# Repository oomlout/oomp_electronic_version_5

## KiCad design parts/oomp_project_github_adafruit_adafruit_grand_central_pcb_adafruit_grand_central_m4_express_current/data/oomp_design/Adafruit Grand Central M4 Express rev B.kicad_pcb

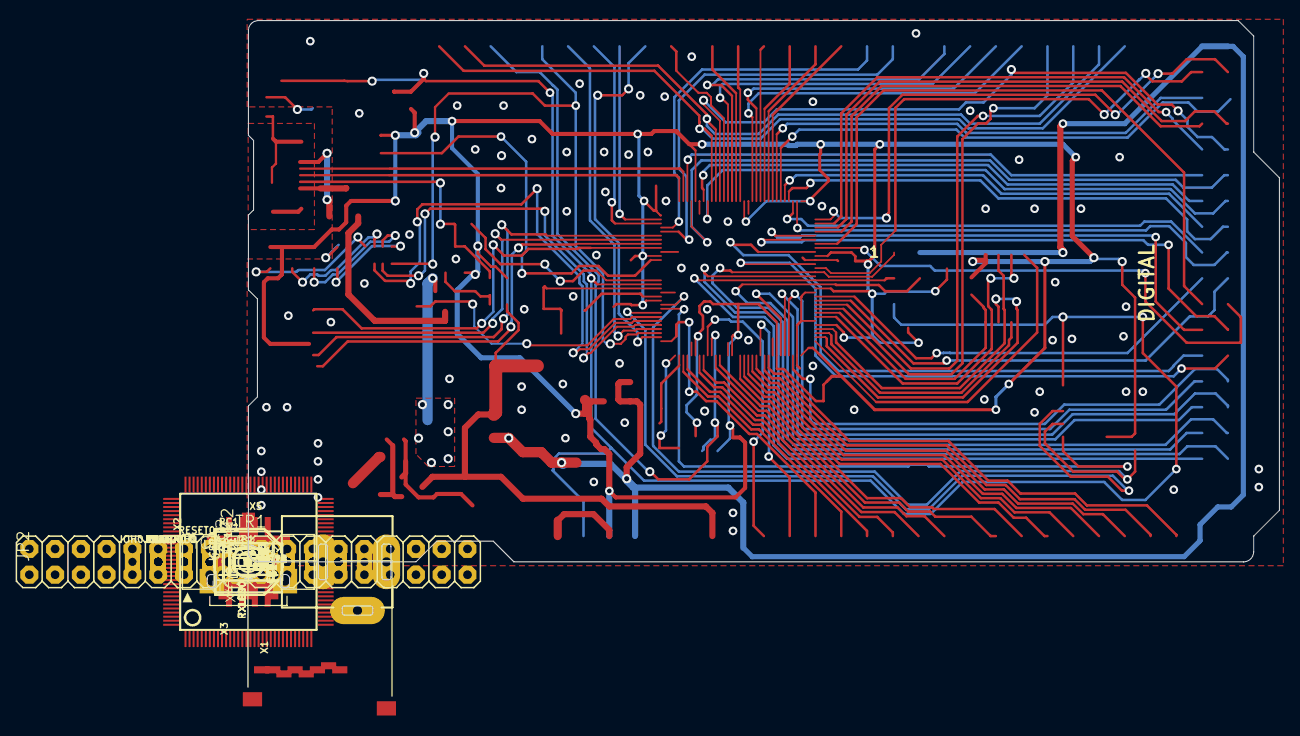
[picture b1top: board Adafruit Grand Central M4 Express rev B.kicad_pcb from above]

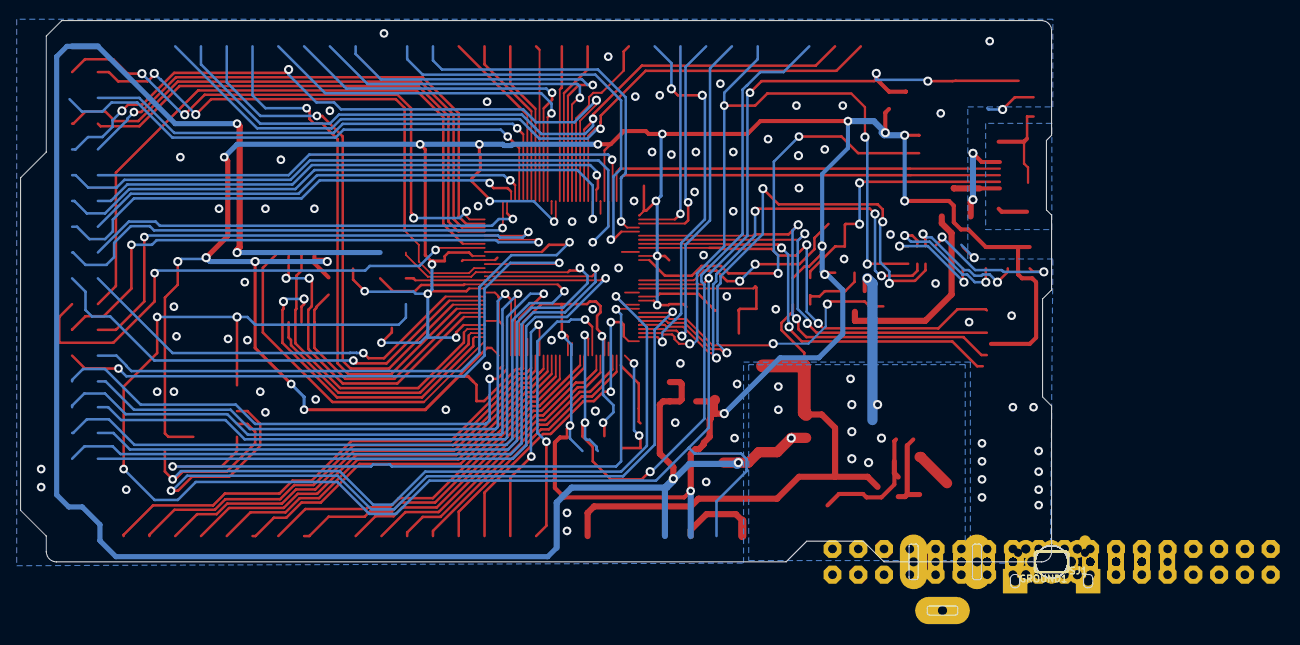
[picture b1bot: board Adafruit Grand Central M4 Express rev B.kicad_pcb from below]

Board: 2 copper layers, 105.7 x 58.6 mm, 81 parts (3 on the bottom side), 113 nets.

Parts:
ANALOGH0: 20610; 1X08_OVALWAVE
ANALOGL0: 20610; 1X08_OVALWAVE
C1, C2, C3: 10uF; 0805-NO
C4, C6, C8, C10, C11, C14, C15, C16, C18, C19, C20, C21, C22, C23, C24, C25: .1u; 0603-NO
C5, C7: 22pF; 0603-NO
C9: 1uF; 0603-NO
C12, C13, C17: 0.1uF; 0603-NO
D1: MBR120; SOD-123
F2: 500mA; R1206
FB2: FERRITE; 0805-NO
FD1, FD2, FD3, FD4, FD5: FIDUCIAL_1MM
GROUND1: SOLDERJUMPER_CLOSEDWIRE
IC3: 74LVC1G125D; SOT23-5
ICSP0: 3x2 M; 2X03_ROUND_70MIL
IOH0: 20611; 1X10_OVALWAVE
IOL0: 20610; 1X08_OVALWAVE
JP1: 1X01_ROUND
JP2: 2X18_THICKWAVE
L0: RED; CHIPLED_0805_NOOUTLINE
L1: 10uH; INDUCTOR_1007
LED1: WS2812B3535; LED3535
ON0: GREEN; CHIPLED_0805_NOOUTLINE
PC1: 47uF/25V; PANASONIC_D
PC2: 47uF+/6.3V+; PANASONIC_D
POWER0: 20610; 1X08_OVALWAVE
R1: 100K; RESPACK_4X0603
R2: 1K; RESPACK_4X0603
R3, R5, R7: 10K; 0603-NO
R4: 1K; 0603-NO
R11: 330R; 0603-NO
RESET0: EVQQ 6mm; EVQ-Q2_SMALLER
RXLED0: YELLOW; CHIPLED_0805_NOOUTLINE
SJ1: AREF_3V; SOLDERJUMPER_CLOSEDWIRE
SW1: SPDT_SMT_SSSS811101
T2: DMP3098L-7; SOT-23
TR1: DMP3098L-7; SOT-23
TXLED0: YELLOW; CHIPLED_0805_NOOUTLINE
U1: NCP1117ST50T3G; SOT223-R
U2: AP2112K-3.3; SOT23-DBV
U3: GD25Q64; SOIC8_208MIL
U$1: SAMD51PXXA; SQFP-S-14X14-128
U$23: GRANDCENTRAL_REVB-BOT
U$30: GRANDCENTRAL_REVB_TOP
UART0: 20610; 1X08_OVALWAVE
UNK_HOLE_0: dummyfp0
UNK_HOLE_1: dummyfp1
UNK_HOLE_2: dummyfp2
UNK_HOLE_3: dummyfp3
UNK_HOLE_4: dummyfp4
UNK_HOLE_5: dummyfp5
X1: microsd; MICROSD
X2: 2x5 0.05" SWD; 2X05_1.27MM_BOX_POSTS
X3: 20329; 4UCONN_20329_V2
X4: 32.768; XTAL3215
X5: 2.1mm; DCJACK_2MM_PTH

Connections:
3.3V: C3.2, C6.2, C10.2, C11.2, C13.1, C14.2, C15.2, C16.2, C18.2, C19.2, C20.2, C21.2, C22.2, C23.2, C24.2, C25.2, IC3.5, LED1.2, ON0.A, POWER0.2, POWER0.4, R1.4, R3.1, R4.2, R5.2, RXLED0.A, SJ1.1, TXLED0.A, U2.5, U3.8, U$1.6, U$1.15, U$1.26, U$1.32, U$1.37, U$1.46, U$1.54, U$1.65, U$1.79, U$1.91, U$1.97, U$1.107, U$1.118, X1.4, X2.1
+5V: C2.2, ICSP0.2, JP2.1, JP2.2, PC2.+, POWER0.5, TR1.2, U1.2, U1.4, U2.1, U2.3
A0: ANALOGL0.1, U$1.9
A1: ANALOGL0.2, U$1.22
A2: ANALOGL0.3, U$1.128
A3: ANALOGL0.4, U$1.3
A4: ANALOGL0.5, U$1.4
A5: ANALOGL0.6, U$1.7
A6: ANALOGL0.7, U$1.8
A7: ANALOGL0.8, U$1.11
A8: ANALOGH0.1, U$1.12
A9: ANALOGH0.2, U$1.17
A10: ANALOGH0.3, U$1.18
A11: ANALOGH0.4, U$1.19
A12: ANALOGH0.5, U$1.20
A13: ANALOGH0.6, U$1.21
A14: ANALOGH0.7, U$1.23
A15: ANALOGH0.8, U$1.24
AREF: C4.1, IOH0.3, SJ1.2, U$1.10
D0: IOL0.8, U$1.101
D1: IOL0.7, U$1.100
D2: IOL0.6, U$1.72
D3: IOL0.5, U$1.73
D4: IOL0.4, U$1.74
D5: IOL0.3, U$1.75
D6: IOL0.2, U$1.80
D7: IOL0.1, U$1.81
D8: IOH0.10, U$1.84
D9: IOH0.9, U$1.127
D10: IOH0.8, U$1.98
D11: IOH0.7, U$1.99
D12: IOH0.6, U$1.125
D13: IOH0.5, R2.8, U$1.126
D22: JP2.3, U$1.51
D23: JP2.4, U$1.63
D44: JP2.25, U$1.55
D45: JP2.26, U$1.52
D46: JP2.27, U$1.29
D47: JP2.28, U$1.30
D48: JP2.29, U$1.27
D49: JP2.30, U$1.28
D+: U$1.95, X3.D+
D-: U$1.94, X3.D-
FLASH_CS: R5.1, U3.1, U$1.40
FLASH_IO0: U3.5, U$1.33
FLASH_IO1: U3.2, U$1.34
FLASH_IO2: U3.3, U$1.35
FLASH_IO3: U3.7, U$1.36
FLASH_SCK: U3.6, U$1.39
GND: C1.2, C2.1, C3.1, C4.2, C5.2, C6.1, C7.2, C8.1, C9.2, C10.1, C11.1, C12.2, C13.2, C14.1, C15.1, C16.1, C17.1, C18.1, C19.1, C20.1, C21.1, C22.1, C23.1, C24.1, C25.1, GROUND1.2, IC3.3, ICSP0.6, IOH0.4, JP2.35, JP2.36, L0.C, LED1.4, PC1.-, PC2.-, POWER0.6, POWER0.7, R1.2, R2.5, RESET0.A, RESET0.A', SW1.A, U1.1, U2.2, U3.4, U$1.5, U$1.14, U$1.25, U$1.31, U$1.38, U$1.45, U$1.53, U$1.64, U$1.78, U$1.90, U$1.96, U$1.106, U$1.116, X1.6, X1.MT1, X1.MT2, X2.3, X2.5, X3.GND, X5.GND, X5.GNDBREAK
MISO: ICSP0.1, JP2.31, U$1.50
MOSI: ICSP0.4, JP2.32, U$1.47
unnamed: L0.A, R2.1
unnamed: FB2.1, GROUND1.1
unnamed: ON0.C, R2.4
unnamed: L1.P$2, U$1.117
unnamed: R2.2, RXLED0.C
unnamed: R2.3, TXLED0.C
unnamed: C5.1, U$1.1, X4.P$1
unnamed: IC3.1, IC3.2, R1.5, R11.1, X3.ID
unnamed: IC3.4, R1.7, R1.8, TR1.3
unnamed: C7.1, U$1.2, X4.P$2
unnamed: D1.C, R7.2, T2.2
NEOPIX: LED1.1, U$1.108
PCC_CLK: JP2.9, U$1.62
PCC_D0: JP2.18, U$1.66
PCC_D1: JP2.17, U$1.67
PCC_D2: JP2.16, U$1.68
PCC_D3: JP2.15, U$1.69
PCC_D4: JP2.14, U$1.88
PCC_D5: JP2.13, U$1.89
PCC_D6: JP2.12, U$1.92
PCC_D7: JP2.11, U$1.93
PCC_D8: JP2.20, U$1.43
PCC_D9: JP2.19, U$1.44
PCC_D10: JP2.22, U$1.56
PCC_D11: JP2.21, U$1.57
PCC_D12: JP2.24, U$1.58
PCC_D13: JP2.23, U$1.59
PCC_DEN1: JP2.7, U$1.60
PCC_DEN2: JP2.8, U$1.61
PCC_XCLK: JP2.10, U$1.85
PWRIN: D1.A, X5.PWR
PWR_SWITCH: JP1.1, R7.1, SW1.B, T2.3
RXLED: R2.7, U$1.124
SCK: ICSP0.3, JP2.33, U$1.48
SCL: IOH0.1, U$1.87, UART0.8
SCL_1: JP2.5, U$1.71
SDA: IOH0.2, U$1.86, UART0.7
SDA_1: JP2.6, U$1.70
SD_CD: U$1.122, X1.CD1
SD_CS: U$1.104, X1.2
SD_MISO: U$1.105, X1.7
SD_MOSI: U$1.102, X1.3
SD_SCK: U$1.103, X1.5
SS: JP2.34, U$1.49
SWCLK: R4.1, U$1.119, X2.4
SWDIO: U$1.120, X2.2
SWO: U$1.121, X2.6
TXLED: R2.6, U$1.123
UART1_RX: U$1.42, UART0.6
UART1_TX: U$1.41, UART0.5
UART2_RX: U$1.77, UART0.4
UART2_TX: U$1.76, UART0.3
UART3_RX: U$1.83, UART0.2
UART3_TX: U$1.82, UART0.1
USBVCC: F2.2, TR1.1
USB_HOSTEN: R11.2, U$1.113
USHIELD: FB2.2, X3.BASE@1, X3.BASE@2, X3.SPRT@1, X3.SPRT@2, X3.SPRT@3, X3.SPRT@4
VBUS: F2.1, X3.VBUS
VDDCORE: C1.1, C8.2, C9.1, L1.P$1, U$1.115
VIN: C12.1, PC1.+, POWER0.8, R1.1, T2.1, U1.3
~RESET: C17.2, ICSP0.5, POWER0.3, R3.2, RESET0.B, RESET0.B', U$1.114, X2.10

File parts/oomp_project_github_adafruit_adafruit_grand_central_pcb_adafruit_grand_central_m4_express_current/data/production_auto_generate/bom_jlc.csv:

Comment,Designator,Footprint,LCSC Part #
,JP1,Adafruit Grand Central M4 Express rev B-import-fps:1X01_ROUND,C7501259
,JP2,Adafruit Grand Central M4 Express rev B-import-fps:2X18_THICKWAVE,
,U$23,Adafruit Grand Central M4 Express rev B-import-fps:GRANDCENTRAL_REVB-BOT,
,U$30,Adafruit Grand Central M4 Express rev B-import-fps:GRANDCENTRAL_REVB_TOP,
,GROUND1,Adafruit Grand Central M4 Express rev B-import-fps:SOLDERJUMPER_CLOSEDWIRE,
,SW1,Adafruit Grand Central M4 Express rev B-import-fps:SPDT_SMT_SSSS811101,
.1u,"C4,C6,C8,C10,C11,C14,C15,C16,C18,C19,C20,C21,C22,C23,C24,C25",Adafruit Grand Central M4 Express rev B-import-fps:0603-NO,
0.1uF,"C12,C13,C17",Adafruit Grand Central M4 Express rev B-import-fps:0603-NO,C14663
100K,R1,Adafruit Grand Central M4 Express rev B-import-fps:RESPACK_4X0603,C25803
10K,"R3,R5,R7",Adafruit Grand Central M4 Express rev B-import-fps:0603-NO,C98220
10uF,"C1,C2,C3",Adafruit Grand Central M4 Express rev B-import-fps:0805-NO,
10uH,L1,Adafruit Grand Central M4 Express rev B-import-fps:INDUCTOR_1007,
1K,R4,Adafruit Grand Central M4 Express rev B-import-fps:0603-NO,C2907002
1K,R2,Adafruit Grand Central M4 Express rev B-import-fps:RESPACK_4X0603,C2907002
1uF,C9,Adafruit Grand Central M4 Express rev B-import-fps:0603-NO,C5673
2.1mm,X5,Adafruit Grand Central M4 Express rev B-import-fps:DCJACK_2MM_PTH,
20329,X3,Adafruit Grand Central M4 Express rev B-import-fps:4UCONN_20329_V2,
20610,"ANALOGH0,ANALOGL0,IOL0,POWER0,UART0",Adafruit Grand Central M4 Express rev B-import-fps:1X08_OVALWAVE,C492421
20611,IOH0,Adafruit Grand Central M4 Express rev B-import-fps:1X10_OVALWAVE,C57369
22pF,"C5,C7",Adafruit Grand Central M4 Express rev B-import-fps:0603-NO,C105620
"2x5 0.05"" SWD",X2,Adafruit Grand Central M4 Express rev B-import-fps:2X05_1.27MM_BOX_POSTS,
32.768,X4,Adafruit Grand Central M4 Express rev B-import-fps:XTAL3215,
330R,R11,Adafruit Grand Central M4 Express rev B-import-fps:0603-NO,C2933198
3x2 M,ICSP0,Adafruit Grand Central M4 Express rev B-import-fps:2X03_ROUND_70MIL,
47uF+/6.3V+,PC2,Adafruit Grand Central M4 Express rev B-import-fps:PANASONIC_D,
47uF/25V,PC1,Adafruit Grand Central M4 Express rev B-import-fps:PANASONIC_D,
500mA,F2,Adafruit Grand Central M4 Express rev B-import-fps:R1206,
74LVC1G125D,IC3,Adafruit Grand Central M4 Express rev B-import-fps:SOT23-5,
AP2112K-3.3,U2,Adafruit Grand Central M4 Express rev B-import-fps:SOT23-DBV,
DMP3098L-7,"T2,TR1",Adafruit Grand Central M4 Express rev B-import-fps:SOT-23,
EVQQ 6mm,RESET0,Adafruit Grand Central M4 Express rev B-import-fps:EVQ-Q2_SMALLER,
FERRITE,FB2,Adafruit Grand Central M4 Express rev B-import-fps:0805-NO,
FIDUCIAL_1MM,"FD1,FD2,FD3,FD4,FD5",Adafruit Grand Central M4 Express rev B-import-fps:FIDUCIAL_1MM,
GD25Q64,U3,Adafruit Grand Central M4 Express rev B-import-fps:SOIC8_208MIL,
GREEN,ON0,Adafruit Grand Central M4 Express rev B-import-fps:CHIPLED_0805_NOOUTLINE,
MBR120,D1,Adafruit Grand Central M4 Express rev B-import-fps:SOD-123,
microsd,X1,Adafruit Grand Central M4 Express rev B-import-fps:MICROSD,
NCP1117ST50T3G,U1,Adafruit Grand Central M4 Express rev B-import-fps:SOT223-R,
RED,L0,Adafruit Grand Central M4 Express rev B-import-fps:CHIPLED_0805_NOOUTLINE,
SAMD51PXXA,U$1,Adafruit Grand Central M4 Express rev B-import-fps:SQFP-S-14X14-128,
WS2812B3535,LED1,Adafruit Grand Central M4 Express rev B-import-fps:LED3535,
YELLOW,"RXLED0,TXLED0",Adafruit Grand Central M4 Express rev B-import-fps:CHIPLED_0805_NOOUTLINE,

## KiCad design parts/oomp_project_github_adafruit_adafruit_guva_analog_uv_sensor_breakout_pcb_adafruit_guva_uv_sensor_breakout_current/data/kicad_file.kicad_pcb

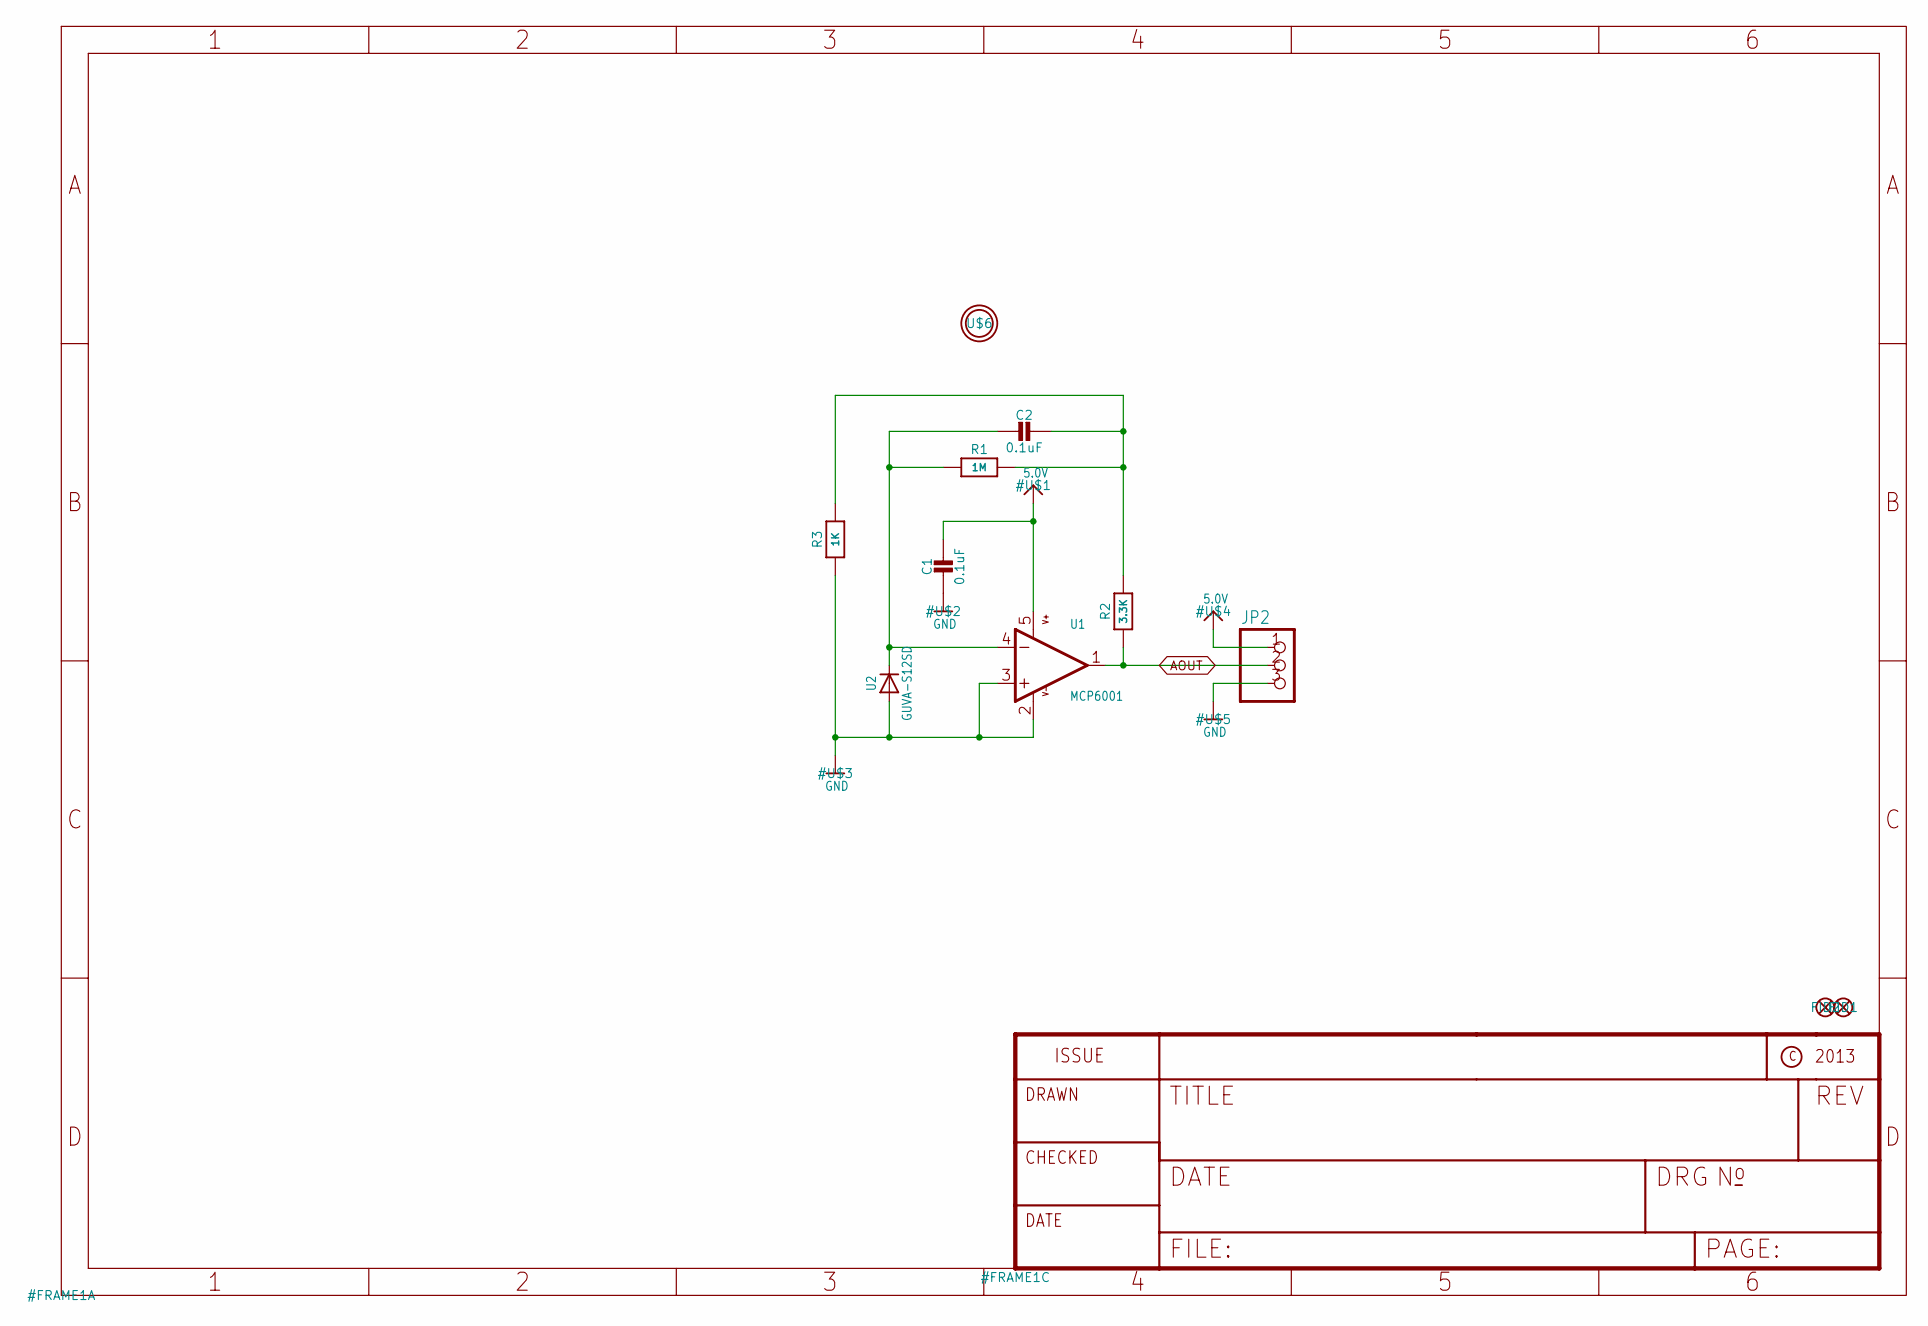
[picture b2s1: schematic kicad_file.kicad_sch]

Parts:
C1, C2: 0.1uF; 0805-NO
FID1, FID2: FIDUCIAL""; FIDUCIAL_1MM
JP2: PINHD-1X3CB; 1X03-CLEANBIG
R1: 1M; 0805-NO
R2: 3.3K; 0805-NO
R3: 1K; 0805-NO
U1: MCP6001; SOT23-5
U2: GUVA-S12SD
U$6: MOUNTINGHOLE2.5; MOUNTINGHOLE_2.5_PLATED

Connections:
5.0V: C1.1, JP2.1, U1.5 (V+)
AOUT: JP2.2, R2.1, U1.1 (OUT)
GND: C1.2, JP2.3, R3.1, U1.2 (V-), U1.3 (+IN), U2.A
unnamed: C2.1, R1.2, R2.2, R3.2
unnamed: C2.2, R1.1, U1.4 (-IN), U2.K (C)

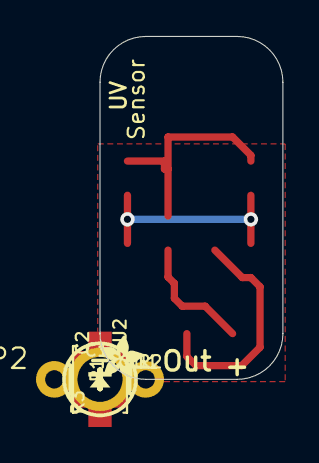
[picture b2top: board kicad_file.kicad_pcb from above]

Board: 2 copper layers, 10.2 x 19.1 mm, 13 parts (1 on the bottom side), 5 nets.

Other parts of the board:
U$7, U$8: ADAFRUIT_2.5MM

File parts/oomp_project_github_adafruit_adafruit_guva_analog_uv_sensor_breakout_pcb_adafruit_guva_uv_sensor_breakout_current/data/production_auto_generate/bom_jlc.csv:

Comment,Designator,Footprint,LCSC Part #
,JP2,Adafruit GUVA UV Sensor Breakout-import-fps:1X03-CLEANBIG,C49257
,"U$7,U$8",Adafruit GUVA UV Sensor Breakout-import-fps:ADAFRUIT_2.5MM,
0.1uF,"C1,C2",Adafruit GUVA UV Sensor Breakout-import-fps:0805-NO,
1K,R3,Adafruit GUVA UV Sensor Breakout-import-fps:0805-NO,C17513
1M,R1,Adafruit GUVA UV Sensor Breakout-import-fps:0805-NO,C2933280
3.3K,R2,Adafruit GUVA UV Sensor Breakout-import-fps:0805-NO,C2907249
GUVA-S12SD,U2,Adafruit GUVA UV Sensor Breakout-import-fps:GUVA-S12SD,
MCP6001,U1,Adafruit GUVA UV Sensor Breakout-import-fps:SOT23-5,

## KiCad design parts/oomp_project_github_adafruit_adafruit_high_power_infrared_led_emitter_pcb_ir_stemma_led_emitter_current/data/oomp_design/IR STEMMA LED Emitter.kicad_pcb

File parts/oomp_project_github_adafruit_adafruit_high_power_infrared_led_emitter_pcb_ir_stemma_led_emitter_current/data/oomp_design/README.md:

# OOMP KiCad design copy

Open `IR STEMMA LED Emitter.kicad_pro` (or the `.kicad_pcb` / `.kicad_sch`) in KiCad. Local OOMP libraries are under `libraries/`. Original inputs are preserved in [../original/](../original/).

Only verified unchanged installed KiCad defaults were renamed. Modified, custom, unmatched and unavailable items remain unchanged. Soldering variants are never swapped during conversion. Existing pad coordinates, nets and UUIDs are preserved.

See [conversion_report.yaml](conversion_report.yaml) for every conversion and skip. Copy this directory before editing; regeneration refuses to overwrite edited design files.

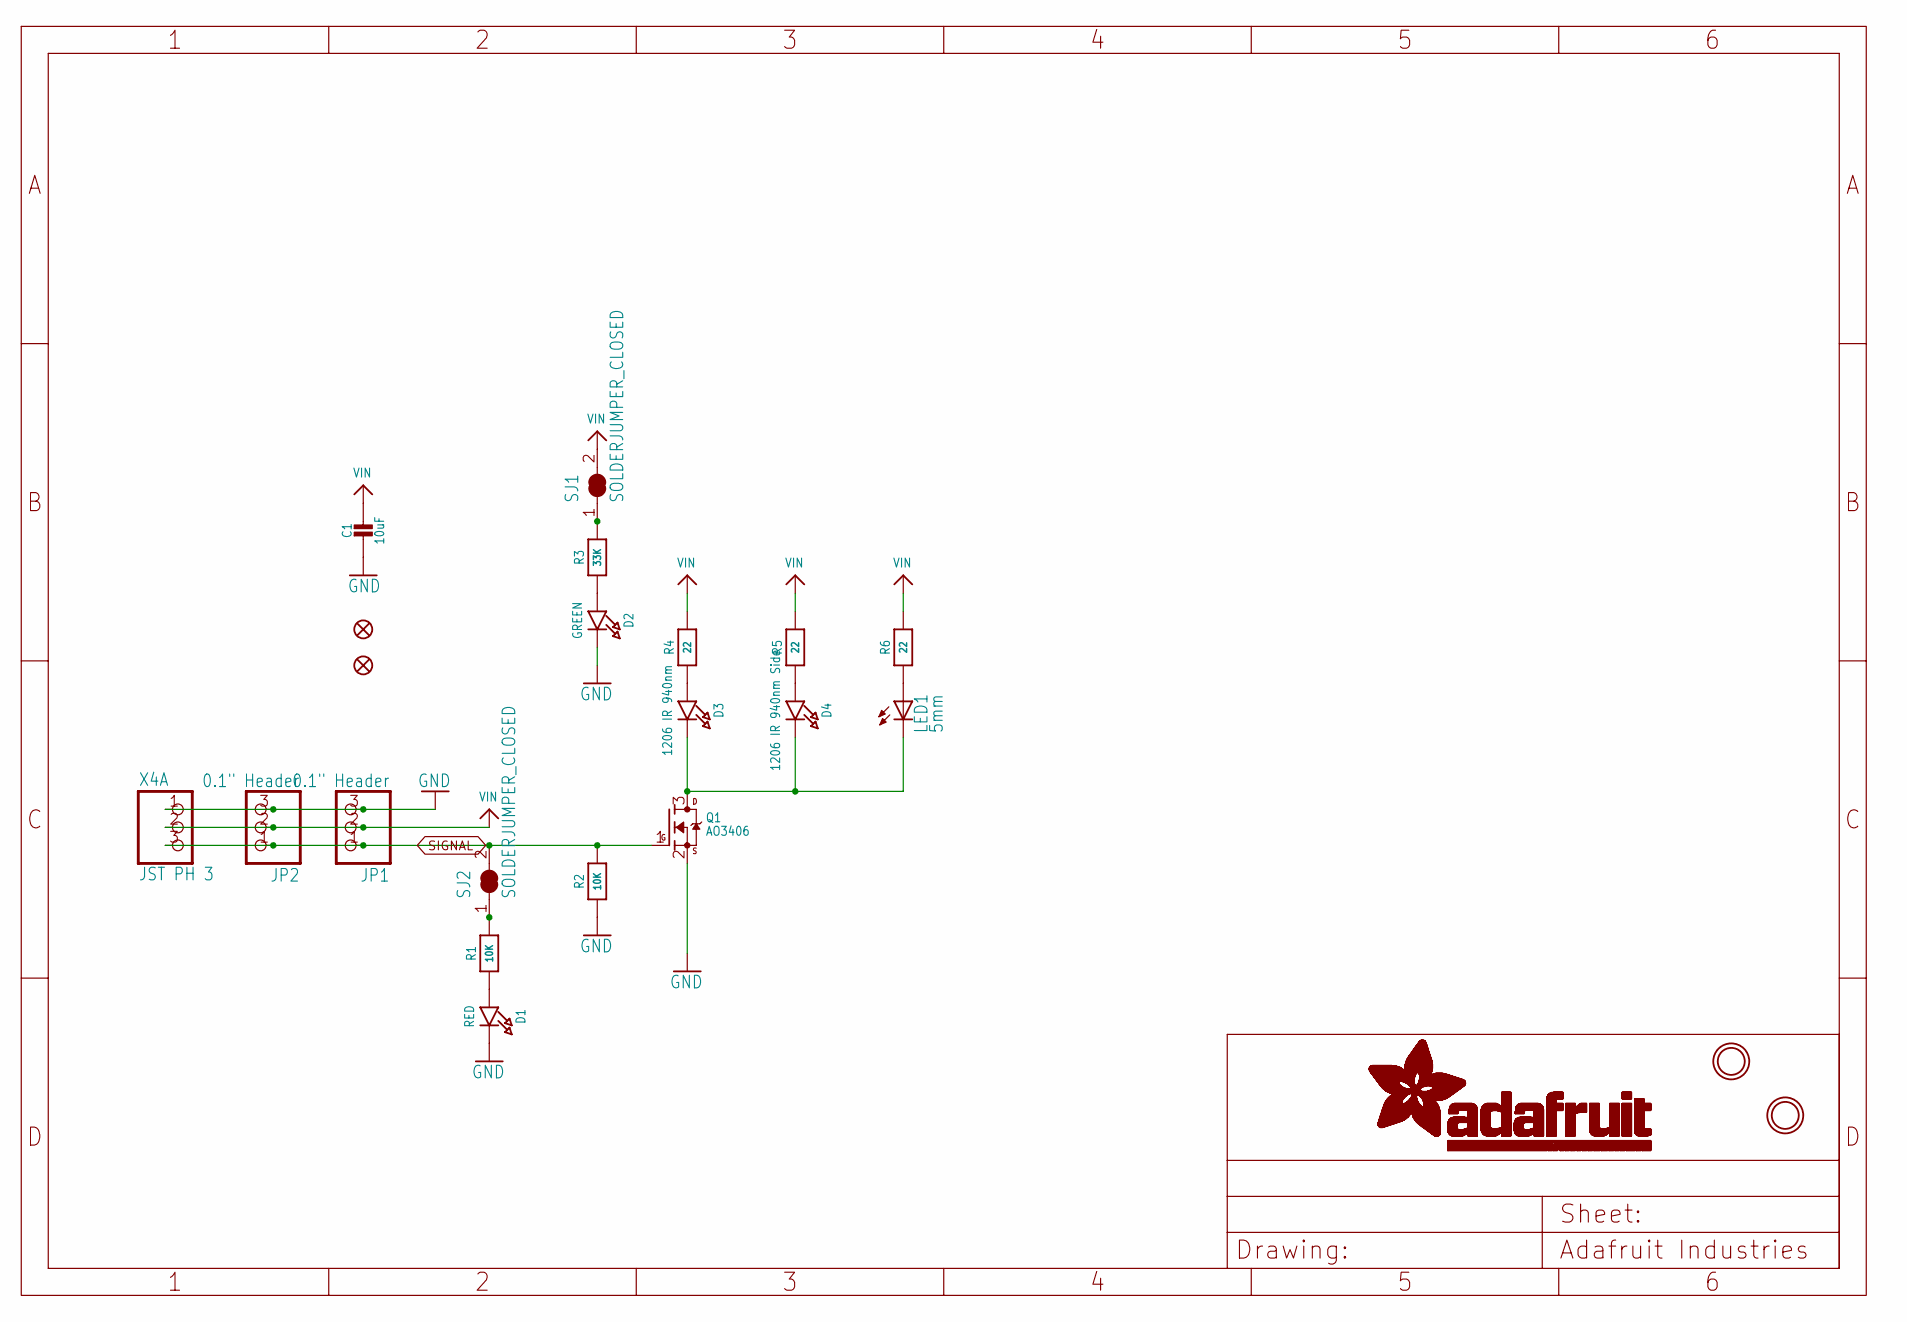
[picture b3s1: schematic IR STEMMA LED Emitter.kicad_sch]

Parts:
C1: 10uF; 0805-NO
D1: RED; CHIPLED_0603_NOOUTLINE
D2: GREEN; CHIPLED_0603_NOOUTLINE
D3: 1206 IR 940nm; CHIPLED_1206
D4: 1206 IR 940nm Side; LED_1206_SIDE
FID2, FID3: FIDUCIAL_1MM
JP1: 0.1" Header; 1X03_OVAL
JP2: 0.1" Header; 1X03_ROUND
LED1: 5mm; LED5MM
Q1: AO3406; SOT23-WIDE
R1, R2: 10K; 0603-NO
R3: 33K; 0603-NO
R4, R5, R6: 22; 0603-NO
SJ1, SJ2: SOLDERJUMPER_CLOSED; SOLDERJUMPER_CLOSEDWIRE
U$1, U$8: MOUNTINGHOLE2.5; MOUNTINGHOLE_2.5_PLATED
X4: JST PH 3; JSTPH3

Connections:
GND: C1.2, D1.C, D2.C, JP1.3, JP2.3, Q1.2 (S), R2.1, X4.1
unnamed: R3.2, SJ1.1
unnamed: D1.A, R1.1
unnamed: R1.2, SJ2.1
unnamed: D3.C, D4.C, LED1.K (C), Q1.3 (D)
unnamed: D3.A, R4.1
unnamed: D4.A, R5.1
unnamed: LED1.A, R6.1
unnamed: D2.A, R3.1
SIGNAL: JP1.1, JP2.1, Q1.1 (G), R2.2, SJ2.2, X4.3
VIN: C1.1, JP1.2, JP2.2, R4.2, R5.2, R6.2, SJ1.2, X4.2

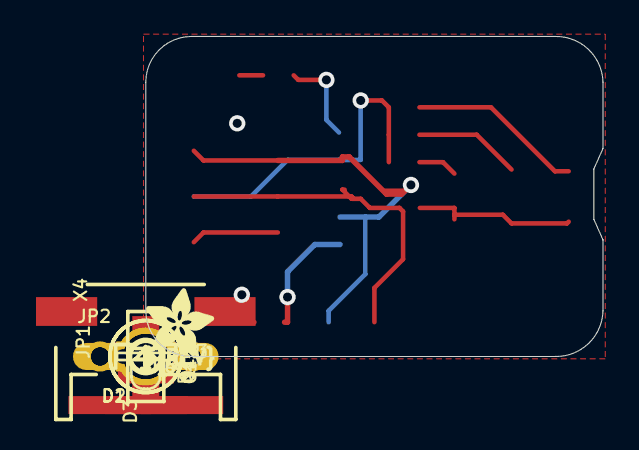
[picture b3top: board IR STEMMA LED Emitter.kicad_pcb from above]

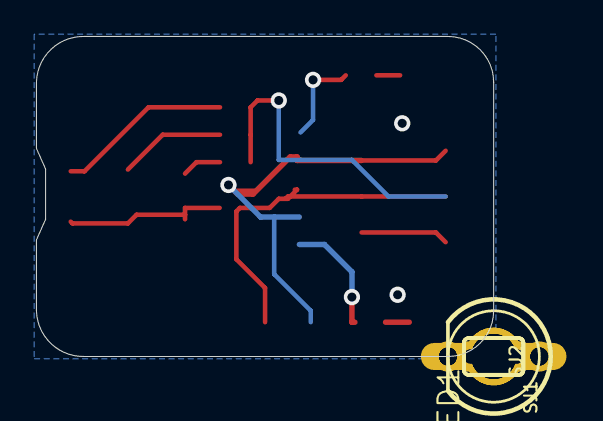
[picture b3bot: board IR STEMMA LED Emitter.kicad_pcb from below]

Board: 16 copper layers, 25.4 x 17.8 mm, 39 parts (14 on the bottom side), 11 nets.

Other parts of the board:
PLABEL0: PLABEL0
PLABEL00: PLABEL00
PLABEL1: PLABEL1
PLABEL2: PLABEL2
PLABEL3: PLABEL3
PLABEL4: PLABEL4
PLABEL5: PLABEL5
PLABEL6: PLABEL6
PLABEL7: PLABEL7
PLABEL8: PLABEL8
PLABEL9: PLABEL9
PLABEL10: PLABEL10
PLABEL11: PLABEL11
PLABEL13: PLABEL13
PLABEL14: PLABEL14
U$5: PCBFEAT-REV-040
U$10: ADAFRUIT_3.5MM

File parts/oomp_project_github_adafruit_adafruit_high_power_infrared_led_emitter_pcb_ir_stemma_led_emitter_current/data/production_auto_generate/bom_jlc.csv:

Comment,Designator,Footprint,LCSC Part #
,U$10,IR STEMMA LED Emitter-import-fps:ADAFRUIT_3.5MM,
,U$5,IR STEMMA LED Emitter-import-fps:PCBFEAT-REV-040,
,PLABEL0,IR STEMMA LED Emitter-import-fps:PLABEL0,
,PLABEL00,IR STEMMA LED Emitter-import-fps:PLABEL00,
,PLABEL1,IR STEMMA LED Emitter-import-fps:PLABEL1,
,PLABEL10,IR STEMMA LED Emitter-import-fps:PLABEL10,
,PLABEL11,IR STEMMA LED Emitter-import-fps:PLABEL11,
,PLABEL13,IR STEMMA LED Emitter-import-fps:PLABEL13,
,PLABEL14,IR STEMMA LED Emitter-import-fps:PLABEL14,
,PLABEL2,IR STEMMA LED Emitter-import-fps:PLABEL2,
,PLABEL3,IR STEMMA LED Emitter-import-fps:PLABEL3,
,PLABEL4,IR STEMMA LED Emitter-import-fps:PLABEL4,
,PLABEL5,IR STEMMA LED Emitter-import-fps:PLABEL5,
,PLABEL6,IR STEMMA LED Emitter-import-fps:PLABEL6,
,PLABEL7,IR STEMMA LED Emitter-import-fps:PLABEL7,
,PLABEL8,IR STEMMA LED Emitter-import-fps:PLABEL8,
,PLABEL9,IR STEMMA LED Emitter-import-fps:PLABEL9,
"0.1"" Header",JP1,IR STEMMA LED Emitter-import-fps:1X03_OVAL,C49257
"0.1"" Header",JP2,IR STEMMA LED Emitter-import-fps:1X03_ROUND,C49257
10K,"R1,R2",IR STEMMA LED Emitter-import-fps:0603-NO,C98220
10uF,C1,IR STEMMA LED Emitter-import-fps:0805-NO,
1206 IR 940nm,D3,IR STEMMA LED Emitter-import-fps:CHIPLED_1206,
1206 IR 940nm Side,D4,IR STEMMA LED Emitter-import-fps:LED_1206_SIDE,
22,"R4,R5,R6",IR STEMMA LED Emitter-import-fps:0603-NO,C23345
33K,R3,IR STEMMA LED Emitter-import-fps:0603-NO,C4216
5mm,LED1,IR STEMMA LED Emitter-import-fps:LED5MM,
AO3406,Q1,IR STEMMA LED Emitter-import-fps:SOT23-WIDE,
GREEN,D2,IR STEMMA LED Emitter-import-fps:CHIPLED_0603_NOOUTLINE,
JST PH 3,X4,IR STEMMA LED Emitter-import-fps:JSTPH3,
RED,D1,IR STEMMA LED Emitter-import-fps:CHIPLED_0603_NOOUTLINE,

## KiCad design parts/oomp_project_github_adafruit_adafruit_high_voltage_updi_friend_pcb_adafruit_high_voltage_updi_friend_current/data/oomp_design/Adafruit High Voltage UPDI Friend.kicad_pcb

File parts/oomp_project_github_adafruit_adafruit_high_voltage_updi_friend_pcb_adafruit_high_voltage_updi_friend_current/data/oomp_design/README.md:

# OOMP KiCad design copy

Open `Adafruit High Voltage UPDI Friend.kicad_pro` (or the `.kicad_pcb` / `.kicad_sch`) in KiCad. Local OOMP libraries are under `libraries/`. Original inputs are preserved in [../original/](../original/).

Only verified unchanged installed KiCad defaults were renamed. Modified, custom, unmatched and unavailable items remain unchanged. Soldering variants are never swapped during conversion. Existing pad coordinates, nets and UUIDs are preserved.

See [conversion_report.yaml](conversion_report.yaml) for every conversion and skip. Copy this directory before editing; regeneration refuses to overwrite edited design files.

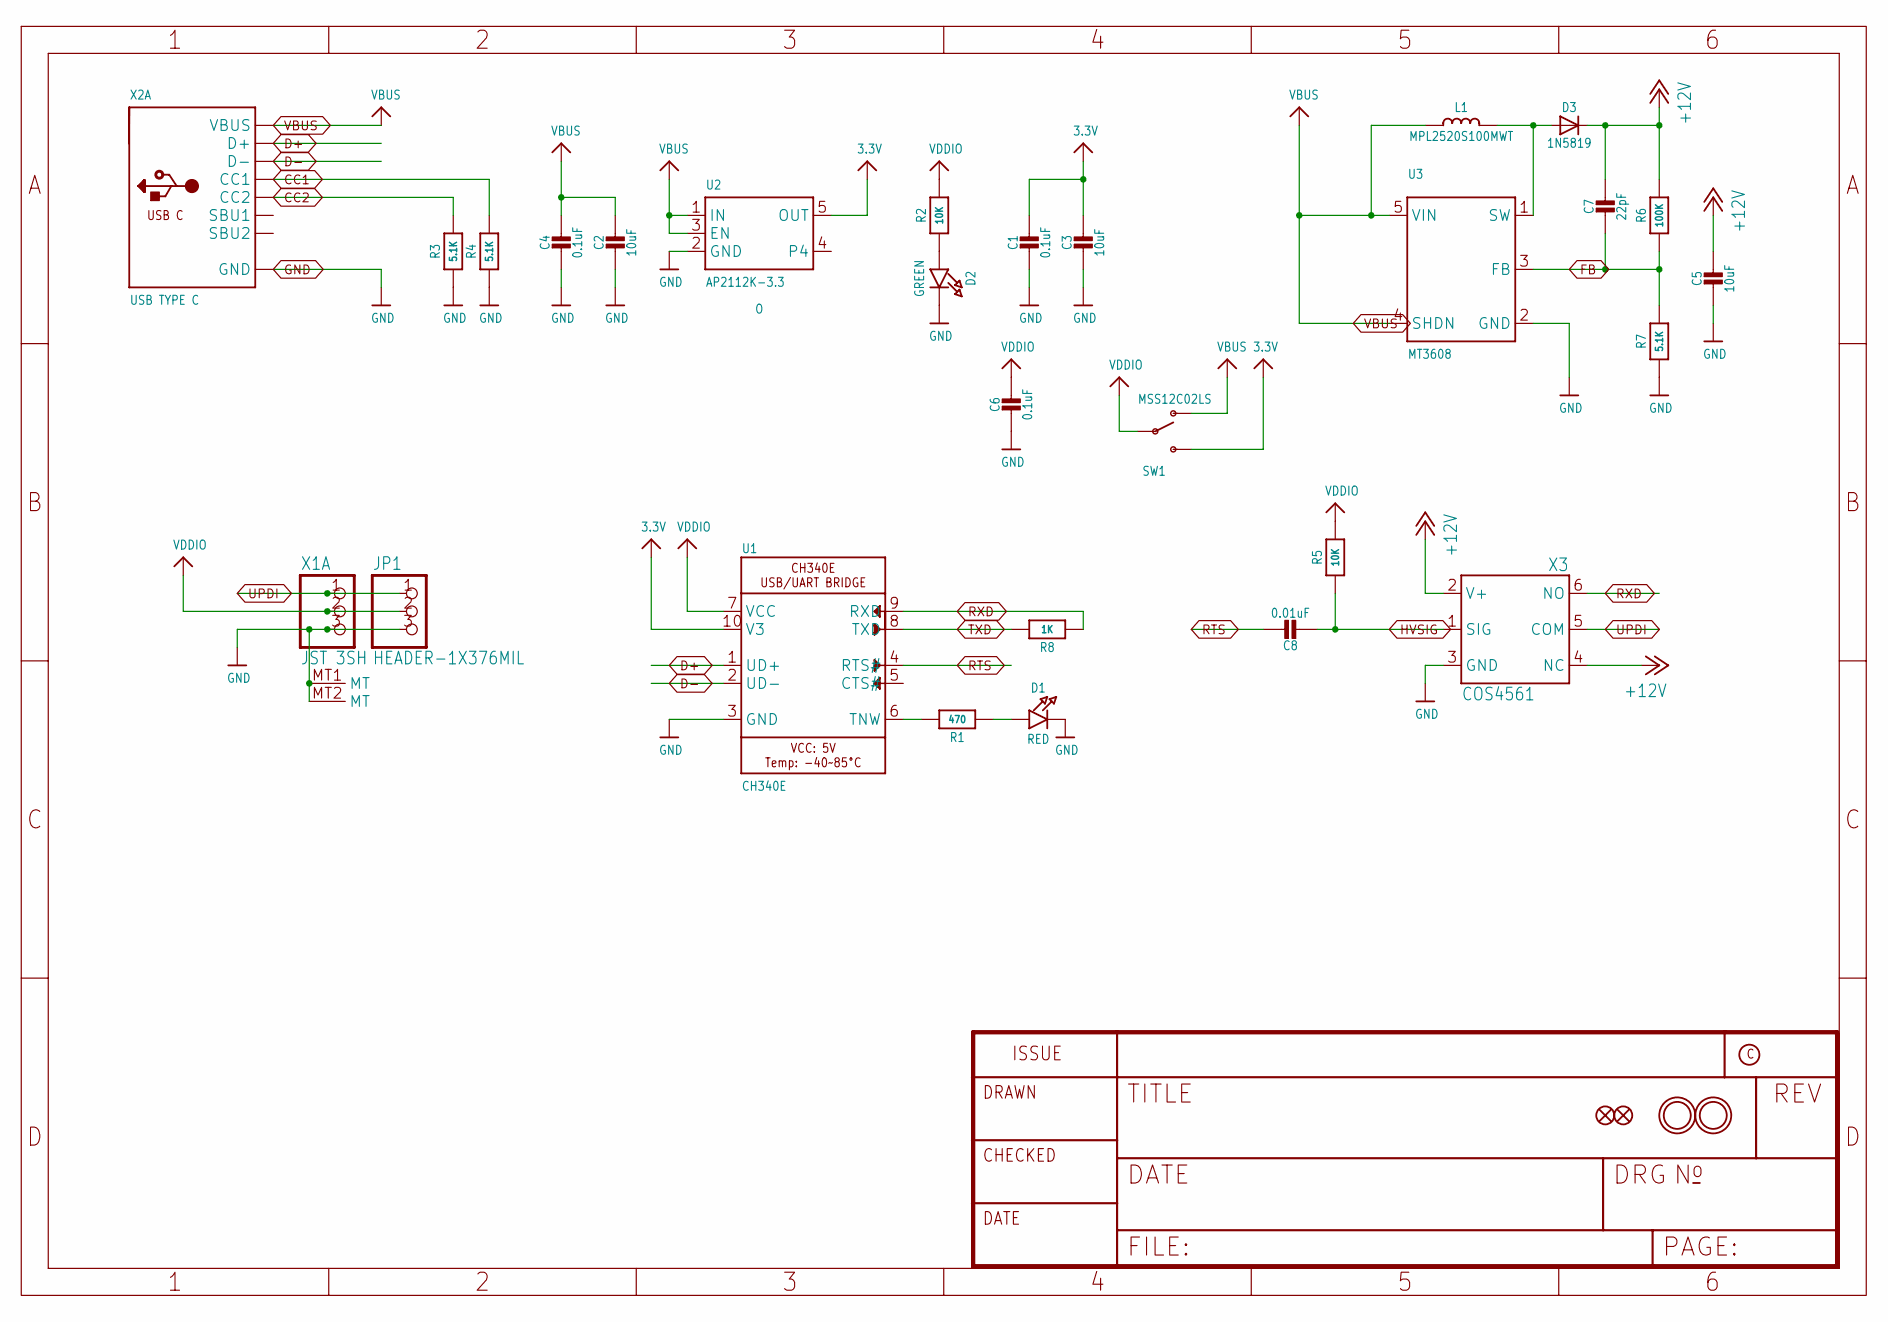
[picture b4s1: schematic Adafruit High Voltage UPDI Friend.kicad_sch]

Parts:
C1, C4, C6: 0.1uF; 0603-NO
C2, C3, C5: 10uF; 0805-NO
C7: 22pF; 0603-NO
C8: 0.01uF; 0603-NO
D1: RED; CHIPLED_0603_NOOUTLINE
D2: GREEN; CHIPLED_0603_NOOUTLINE
D3: 1N5819; SOD-323
FID1, FID2: FIDUCIAL_1MM
JP1: HEADER-1X376MIL; 1X03_ROUND_76
L1: MPL2520S100MWT; INDUCTOR_1007
R1: 470; 0603-NO
R2, R5: 10K; 0603-NO
R3, R4, R7: 5.1K; 0603-NO
R6: 100K; 0603-NO
R8: 1K; 0603-NO
SW1: MSS12C02LS; SPDT_SMT_SSSS811101
U1: CH340E; MSOP10
U2: AP2112K-3.3; SOT23-5; JLC_ROTATION 0
U3: MT3608; SOT23-6
U$18, U$19: MOUNTINGHOLE2.0; MOUNTINGHOLE_2.0_PLATED
X1: JST 3SH; JST_SH3
X2: USB TYPE C; USB_C_CUSB31-CFM2AX-01-X; LCSC C165948
X3: COS4561; SOT23-6

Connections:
3.3V: C1.1, C3.1, SW1.C (S), U1.10 (V3), U2.5 (OUT)
+12V: C5.1, C7.1, D3.C, R6.2, X3.2 (V+), X3.4 (NC)
CC1: R4.2, X2.A5 (CC1)
CC2: R3.2, X2.B5 (CC2)
D+: U1.1 (UD+), X2.A6 (D+), X2.B6 (D+)
D-: U1.2 (UD-), X2.A7 (D-), X2.B7 (D-)
FB: C7.2, R6.1, R7.2, U3.3 (FB)
GND: C1.2, C2.2, C3.2, C4.2, C5.2, C6.2, D1.C, D2.C, JP1.3, R3.1, R4.1, R7.1, U1.3 (GND), U2.2 (GND), U3.2 (GND), X1.3, X1.MT1 (MT), X1.MT2 (MT), X2.A1B12 (GND), X2.B1A12 (GND), X3.3 (GND)
HVSIG: C8.2, R5.1, X3.1 (SIG)
unnamed: D1.A, R1.1
unnamed: R1.2, U1.6 (TNW)
unnamed: D3.A, L1.P$2 (2), U3.1 (SW)
unnamed: D2.A, R2.1
RTS: C8.1, U1.4 (RTS#)
RXD: R8.2, U1.9 (RXD), X3.6 (NO)
TXD: R8.1, U1.8 (TXD)
UPDI: JP1.1, X1.1, X3.5 (COM)
VBUS: C2.1, C4.1, L1.P$1 (1), SW1.A (O), U2.1 (IN), U2.3 (EN), U3.4 (SHDN), U3.5 (VIN), X2.A4B9 (VBUS), X2.B4A9 (VBUS)
VDDIO: C6.1, JP1.2, R2.2, R5.2, SW1.B, U1.7 (VCC), X1.2

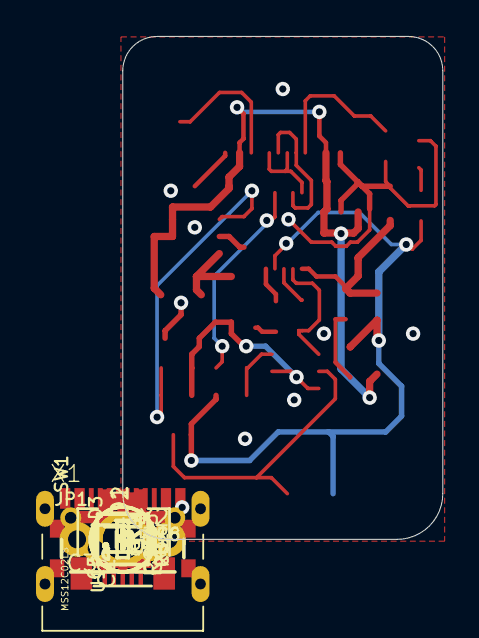
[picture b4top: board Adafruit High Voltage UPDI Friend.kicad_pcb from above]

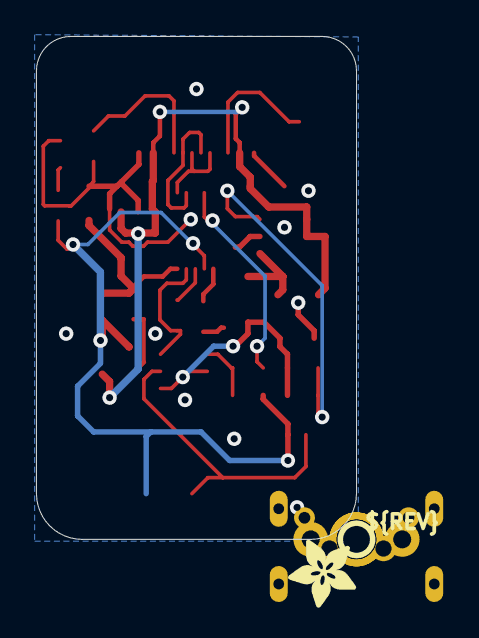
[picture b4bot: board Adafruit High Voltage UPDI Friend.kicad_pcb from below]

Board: 2 copper layers, 17.8 x 27.9 mm, 46 parts (7 on the bottom side), 19 nets.

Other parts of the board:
PLABEL0: PLABEL0
PLABEL1: PLABEL1
PLABEL2: PLABEL2
PLABEL3: PLABEL3
PLABEL4: PLABEL4
PLABEL5: PLABEL5
PLABEL6: PLABEL6
PLABEL7: PLABEL7
PLABEL8: PLABEL8
PLABEL9: PLABEL9
PLABEL10: PLABEL10
PLABEL11: PLABEL11
U$17: PCBFEAT-REV-040
U$36: ADAFRUIT_3.5MM

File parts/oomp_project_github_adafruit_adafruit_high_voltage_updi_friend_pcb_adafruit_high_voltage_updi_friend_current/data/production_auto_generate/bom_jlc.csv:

Comment,Designator,Footprint,LCSC Part #
,JP1,Adafruit High Voltage UPDI Friend-import-fps:1X03_ROUND_76,C49257
,U$36,Adafruit High Voltage UPDI Friend-import-fps:ADAFRUIT_3.5MM,
,U$17,Adafruit High Voltage UPDI Friend-import-fps:PCBFEAT-REV-040,
,PLABEL0,Adafruit High Voltage UPDI Friend-import-fps:PLABEL0,
,PLABEL1,Adafruit High Voltage UPDI Friend-import-fps:PLABEL1,
,PLABEL10,Adafruit High Voltage UPDI Friend-import-fps:PLABEL10,
,PLABEL11,Adafruit High Voltage UPDI Friend-import-fps:PLABEL11,
,PLABEL2,Adafruit High Voltage UPDI Friend-import-fps:PLABEL2,
,PLABEL3,Adafruit High Voltage UPDI Friend-import-fps:PLABEL3,
,PLABEL4,Adafruit High Voltage UPDI Friend-import-fps:PLABEL4,
,PLABEL5,Adafruit High Voltage UPDI Friend-import-fps:PLABEL5,
,PLABEL6,Adafruit High Voltage UPDI Friend-import-fps:PLABEL6,
,PLABEL7,Adafruit High Voltage UPDI Friend-import-fps:PLABEL7,
,PLABEL8,Adafruit High Voltage UPDI Friend-import-fps:PLABEL8,
,PLABEL9,Adafruit High Voltage UPDI Friend-import-fps:PLABEL9,
0.01uF,C8,Adafruit High Voltage UPDI Friend-import-fps:0603-NO,C5137477
0.1uF,"C1,C4,C6",Adafruit High Voltage UPDI Friend-import-fps:0603-NO,C14663
100K,R6,Adafruit High Voltage UPDI Friend-import-fps:0603-NO,C25803
10K,"R2,R5",Adafruit High Voltage UPDI Friend-import-fps:0603-NO,C98220
10uF,"C2,C3,C5",Adafruit High Voltage UPDI Friend-import-fps:0805-NO,
1K,R8,Adafruit High Voltage UPDI Friend-import-fps:0603-NO,C2907002
1N5819,D3,Adafruit High Voltage UPDI Friend-import-fps:SOD-323,
22pF,C7,Adafruit High Voltage UPDI Friend-import-fps:0603-NO,C105620
470,R1,Adafruit High Voltage UPDI Friend-import-fps:0603-NO,C23179
5.1K,"R3,R4,R7",Adafruit High Voltage UPDI Friend-import-fps:0603-NO,C23186
AP2112K-3.3,U2,Adafruit High Voltage UPDI Friend-import-fps:SOT23-5,
CH340E,U1,Adafruit High Voltage UPDI Friend-import-fps:MSOP10,
COS4561,X3,Adafruit High Voltage UPDI Friend-import-fps:SOT23-6,
GREEN,D2,Adafruit High Voltage UPDI Friend-import-fps:CHIPLED_0603_NOOUTLINE,
JST 3SH,X1,Adafruit High Voltage UPDI Friend-import-fps:JST_SH3,C265338
MPL2520S100MWT,L1,Adafruit High Voltage UPDI Friend-import-fps:INDUCTOR_1007,
MSS12C02LS,SW1,Adafruit High Voltage UPDI Friend-import-fps:SPDT_SMT_SSSS811101,
MT3608,U3,Adafruit High Voltage UPDI Friend-import-fps:SOT23-6,
RED,D1,Adafruit High Voltage UPDI Friend-import-fps:CHIPLED_0603_NOOUTLINE,
USB TYPE C,X2,Adafruit High Voltage UPDI Friend-import-fps:USB_C_CUSB31-CFM2AX-01-X,
